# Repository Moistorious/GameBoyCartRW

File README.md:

# GameBoyCartRW

A simple (and incredibly slow) Arduino Nano based Gameboy cart reader/writer.

## Important

**Do not insert a GBA Cartridge!**

I don't know if GBA Carts are 5v tolerant, so it's possible that this would damage the cartridge!

**The PCB files are incorrect**! I currently have bodge wires between A6->D3 and A7->D13. This should be fixed in a future revision (If I get around to it)

## Utilities

The UI uses Windows forms

The Firmware project was done using PlatformIO in VSCode

PCB was designed with EasyEDA

Cartridge slot is a replacement [GBA cart slot](https://www.aliexpress.com/item/1005005016059093.html?spm=a2g0o.order_list.order_list_main.41.42031802yNwN0F)

## Features

* Make backups of cartridge ROMs

* Make backups of cartridge SRAM

* Write backups to cartridge SRAM

## Supported Cartridges

As far as I'm aware, all features should with any Gameboy/Gameboy Colour cartridge.

## References

[GBDev.io Pan Docs](https://gbdev.io/pandocs) is an absolutely phenomenal resource with all the information you could possibly want.

I used Inside Gadgets' "[GBCartRead](https://github.com/insidegadgets/GBCartRead)" as a resource when I was having issues.

## License

[MIT](https://choosealicense.com/licenses/mit/)

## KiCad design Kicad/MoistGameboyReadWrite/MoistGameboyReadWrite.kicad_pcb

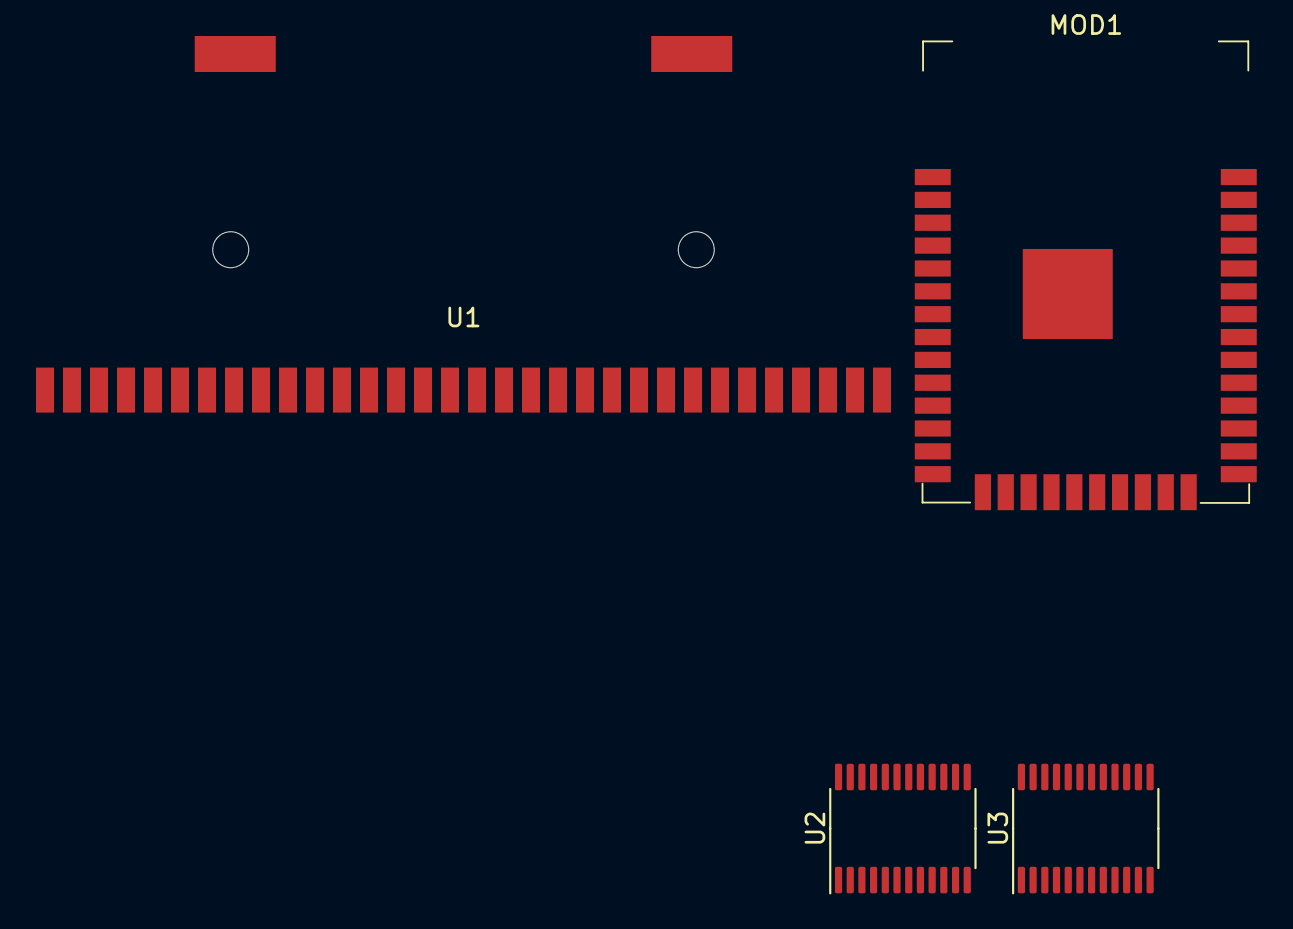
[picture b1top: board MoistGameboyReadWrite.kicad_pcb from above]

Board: 2 copper layers, 4 parts (0 on the bottom side), 2 nets, no tracks yet.

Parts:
MOD1: ESP32-WROOM-32; ESP32-WROOM-32D
U1: CartBus; DSL_Cartridge_Reader
U2, U3: PCAL6416APW; TSSOP-24_4.4x7.8mm_P0.65mm

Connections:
SCL: MOD1.21 (SDO/SD0), U2.22 (SCL), U3.22 (SCL)
SDA: MOD1.22 (SDI/SD1), U2.23 (SDA), U3.23 (SDA)

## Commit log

2022-09-24 Just saving ithe code
2023-10-11 Moving into subfolders, adding C# project
2023-10-12 Adding UI, added reading/writing RAM, no longer hardcoded to a folder on my desktop Added serial command to reset the cart (maybe useful?)
2023-10-12 Improving UI, adding some unsafe code to improve cart header parsing
2023-10-13 Adding unit test project, some refactoring
2023-10-13 Adding PCB and Readme
2023-10-13 Removing unneeded vscode config
2023-10-13 Adding pictures of circuit board
2023-10-15 improving performance! still some bugs with progress bar though
2023-10-15 Trying to learn kicad
2023-10-17 Breaking things!
2023-10-17 fixing the RAM Write
